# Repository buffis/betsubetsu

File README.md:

# BetsuBetsu

BetsuBetsu is an Open Source Audio+Video splitter for streaming/recording video from Arcade games (Jamma).

It plugs in between the game and cabinet, and can then be connected to any upscaler + PC for streaming/recording.

## Features
- MiniDIN 8 RGB video out (same pins as XRGB-Mini, HAS,...), for hooking it up to OSSC.
- Mono audio output through audio jack.
- Adjustable RGB video levels through onboard trimpots.
- Audio gain can be fine tuned through onboard trimpot.
- Power LED
- Optional Voltmeter can be attached

## More detailed features
- Line level audio conversion with galvanic isolation (TY-250P).
- Buffering and unbiasing of Video and Sync signals to safe levels (THS7374). Inputs and outputs are AC-coupled. Safe to drive 75ohm loads / OSSC.
- Audio completely isolated from video (no common ground) to avoid ground loop noise.

## Build instructions

- Order a pcb. Kicad plot files are in the plot/ subdir in the repo.
- Order all parts needed (see BOM)
- Solder it up (suggested order below)
  - Start with THS7374. It's the trickiest footprint to solder.
  - Then do all 0805-sized parts in any order.
  - Solder all five big capacitors. Note that the bottom one is 100uF
  - Solder all trimpots
  - Solder the transformer + output jacks
  - Finally add the Jamma connector (make sure to put it on Jamma In)
- (Optional) Add a voltmeter.

## Installation instructions

1. Insert the BetsuBetsu into the cab jamma harness and connect the game.
2. Connect "Audio Out" to the PC line-in with a stereo cable.
3. Connect "Video Out" to a OSSC or XRGB-Mini with a MINI-DIN8 to SCART cable
4. Connect OSSC/XRGB-Mini to a Capture card (I recomment USB3HDCAP)
5. Capture/Stream in OBS.
6. Calibrate strength of video signals with onboard trimpots
7. Audio output can be fine-adjusted with onboard "Audio" trimpot.

## Schematic (v1.0):

## Board:

## BOM:
https://docs.google.com/spreadsheets/d/1Nb6cgpz1vrsEBL83Tl52jcXvUmsp_AzcXZ7w7m8aYmA/edit?usp=sharing

## Sample capture:
BetsuBetsu + OSSC + Elgato 60 Pro. Scaled to fit inside 1080p in OBS.
Audio is wired from Betsu Betsu to PC Line in directly.
https://www.youtube.com/watch?v=HWDo_Xj9CUc

BetsuBetsu + XRGB-Mini + Elgato 60 Pro. Scaled to fit inside 1080p in OBS.
Audio is wired from Betsu Betsu to PC Line in directly.
https://www.youtube.com/watch?v=Qm8Wi2TviPc

## Misc links:
Arcade-projects thread:
https://www.arcade-projects.com/forums/index.php?thread/10551-betsu-betsu-open-source-arcade-audio-video-splitter-for-capture-streaming/

## Misc pics:
Action shot of prototype board in cab:

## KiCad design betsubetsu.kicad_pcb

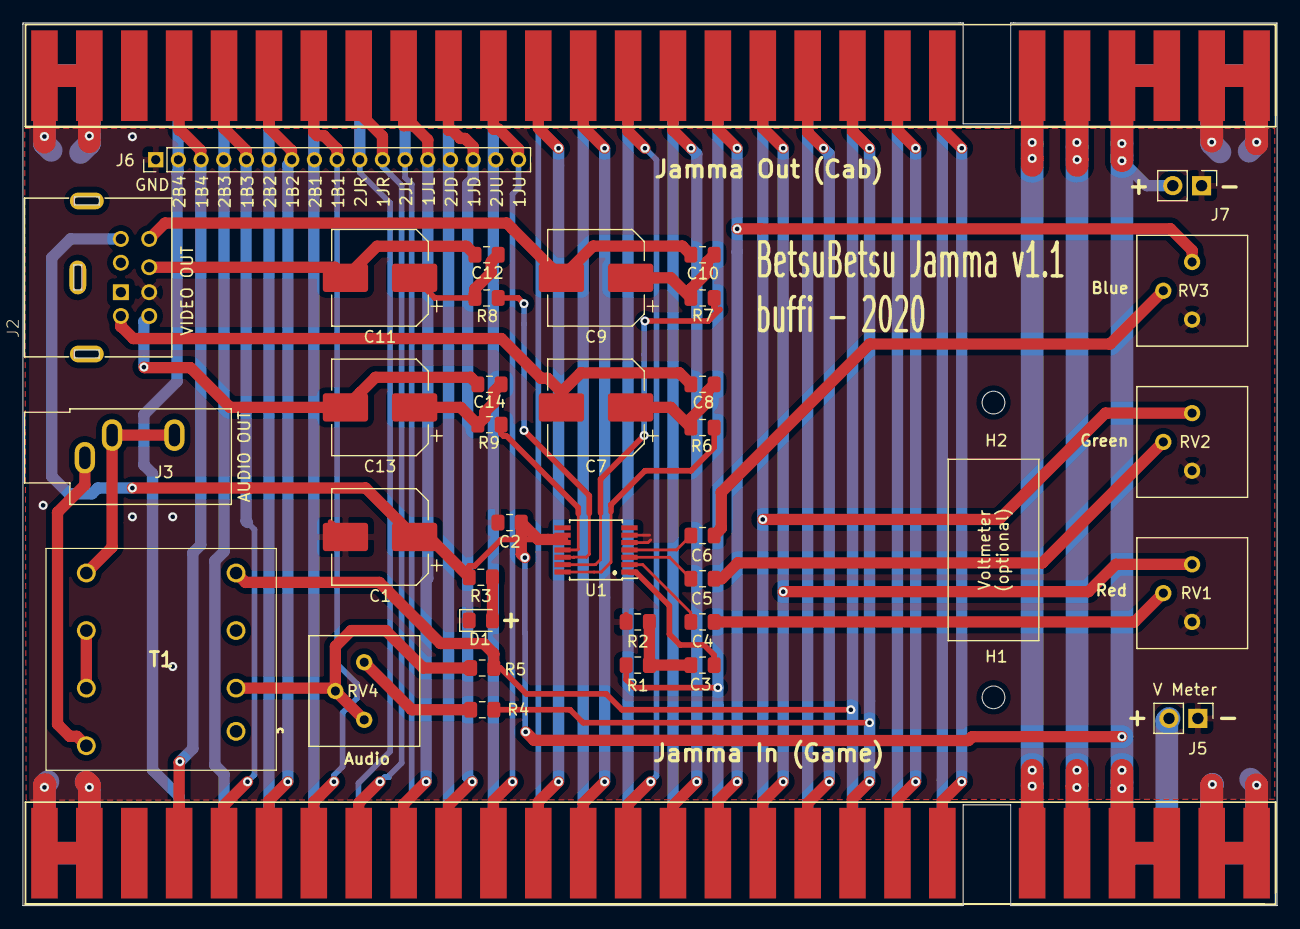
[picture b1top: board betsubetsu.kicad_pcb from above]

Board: 2 copper layers, 110.6 x 77.9 mm, 39 parts (0 on the bottom side), 66 nets.

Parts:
C1: 100u; CP_Elec_8x6.7
C2, C3, C4, C5, C6, C8, C10, C12, C14: 0.1u; C_0805_2012Metric_Pad1.15x1.40mm_HandSolder
C7, C9, C11, C13: 470u; CP_Elec_8x6.7
D1: LED; LED_0805_2012Metric_Pad1.15x1.40mm_HandSolder
H1, H2: V METER HOLE (2mm); MountingHole_2mm
J1: Jamma Out (Cab); JAMMA-56
J2: VIDEO OUT; MD-80SM
J3: AUDIO OUT; Jack_3.5mm_CUI_SJ1-3533NG_Horizontal
J4: Jamma In (Game); JAMMA-56
J5: V Meter; PinHeader_1x02_P2.54mm_Vertical
J6: Conn_01x17; PinHeader_1x17_P2.00mm_Vertical
J7: 5V; PinHeader_1x02_P2.54mm_Vertical
R1: 1k; R_0805_2012Metric_Pad1.15x1.40mm_HandSolder
R2: 150; R_0805_2012Metric_Pad1.15x1.40mm_HandSolder
R3, R4: 390; R_0805_2012Metric_Pad1.15x1.40mm_HandSolder
R5: 47; R_0805_2012Metric_Pad1.15x1.40mm_HandSolder
R6, R7, R8, R9: 75; R_0805_2012Metric_Pad1.15x1.40mm_HandSolder
RV1, RV2, RV3: 1K; Potentiometer_Bourns_3386P_Vertical
RV4: 500; Potentiometer_Bourns_3386P_Vertical
T1: TY-250P; TY250P
U1: THS7374; TSSOP-14_4.4x5mm_P0.65mm

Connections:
+5V: C1.1, C2.2, J1.3, J1.4, J1.C, J1.D, J2.5, J4.3, J4.4, J4.C, J4.D, J5.2, J7.2, R3.2, U1.9, U1.10
+12V: J1.6, J1.F, J4.6, J4.F
+AUDIO_IN: J1.10, J4.10, R4.1
-5V: J1.5, J1.E, J4.5, J4.E
-AUDIO_IN: J1.L, J4.L, R5.1, T1.4
BLUE_IN: J1.13, J4.13, RV3.1
BLUE_OUT: C13.2, C14.1, J2.6
COIN1: J1.16, J4.16
COIN2: J1.T, J4.T
CSYNC_OUT: C7.2, C8.1, J2.3
GND: C1.2, C2.1, D1.1, J1.1, J1.2, J1.27, J1.28, J1.A, J1.B, J1.e, J1.f, J2.4, J4.1, J4.2, J4.27, J4.28, J4.A, J4.B, J4.e, J4.f, J5.1, J6.1, J7.1, R2.1, RV1.3, RV2.3, RV3.3, U1.5, U1.6
GREEN_IN: J1.N, J4.N, RV2.1
GREEN_OUT: C11.2, C12.1, J2.7
LOCKOUT1: J1.9, J4.9
LOCKOUT2: J1.K, J4.K
METER1: J1.8, J4.8
METER2: J1.J, J4.J
unnamed: C3.1, U1.1
unnamed: C3.2, R1.1, R2.2
unnamed: C4.1, U1.2
unnamed: C4.2, RV1.2
unnamed: C5.1, U1.3
unnamed: C5.2, RV2.2
unnamed: C6.1, U1.4
unnamed: C6.2, RV3.2
unnamed: C7.1, C8.2, R6.1
unnamed: C9.1, C10.2, R7.1
unnamed: C11.1, C12.2, R8.1
unnamed: C13.1, C14.2, R9.1
unnamed: D1.2, R3.1
unnamed: J3.R, J3.T, T1.5
unnamed: J3.S, T1.8
unnamed: R4.2, RV4.1
unnamed: R5.2, RV4.2, RV4.3, T1.2
unnamed: R6.2, U1.14
unnamed: R7.2, U1.13
unnamed: R8.2, U1.12
unnamed: R9.2, U1.11
unnamed: T1.6, T1.7
P1_A: J1.22, J4.22, J6.9
P1_B: J1.23, J4.23, J6.7
P1_C: J1.24, J4.24, J6.5
P1_D: J1.25, J4.25, J6.3
P1_DOWN: J1.19, J4.19, J6.15
P1_LEFT: J1.20, J4.20, J6.13
P1_RIGHT: J1.21, J4.21, J6.11
P1_START: J1.17, J4.17
P1_UP: J1.18, J4.18, J6.17
P2_A: J1.Z, J4.Z, J6.8
P2_B: J1.a, J4.a, J6.6
P2_C: J1.b, J4.b, J6.4
P2_D: J1.c, J4.c, J6.2
P2_DOWN: J1.W, J4.W, J6.14
P2_LEFT: J1.X, J4.X, J6.12
P2_RIGHT: J1.Y, J4.Y, J6.10
P2_START: J1.U, J4.U
P2_UP: J1.V, J4.V, J6.16
RED_IN: J1.12, J4.12, RV1.1
RED_OUT: C9.2, C10.1, J2.8
SERVICE: J1.R, J4.R
SYNC_IN: J1.P, J4.P, R1.2
TEST: J1.15, J4.15
TILT: J1.S, J4.S
UNUSED11: J1.11, J4.11
UNUSED39: J1.M, J4.M
VIDEO_GND: J1.14, J4.14

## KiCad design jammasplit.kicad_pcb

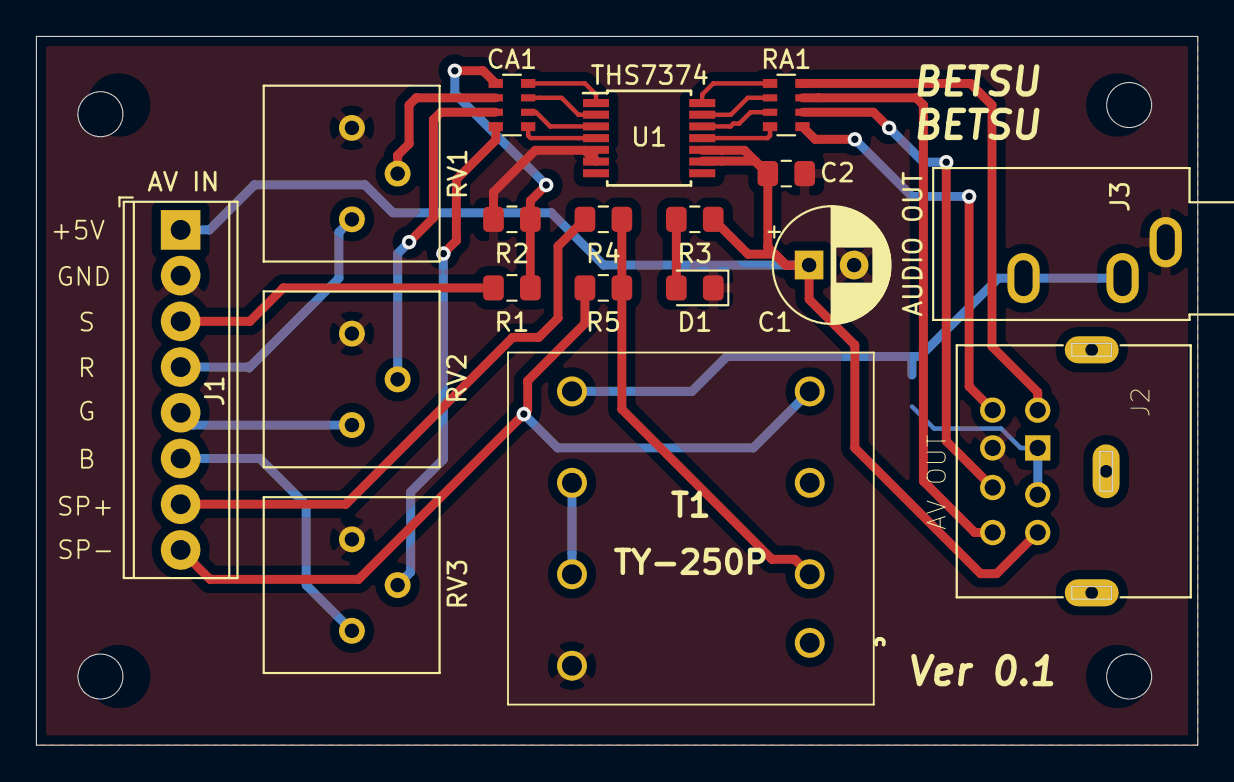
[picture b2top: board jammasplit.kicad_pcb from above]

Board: 2 copper layers, 64.5 x 39.4 mm, 23 parts (1 on the bottom side), 29 nets.

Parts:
C1: 100uF; CP_Radial_D6.3mm_P2.50mm
C2: 0.1uF; C_0805_2012Metric_Pad1.15x1.40mm_HandSolder
CA1: CapacitorArray4; R_Array_Convex_4x0603
D1: LED; LED_0805_2012Metric_Pad1.15x1.40mm_HandSolder
H1, H2, H3, H4: MountingHole; MountingHole_2.5mm
J1: AV IN; TerminalBlock_Phoenix_MPT-0,5-8-2.54_1x08_P2.54mm_Horizontal
J2: AV OUT; CUI_MD-80SM
J3: AUDIO OUT; Jack_3.5mm_CUI_SJ1-3533NG_Horizontal
JMP1: SCART_AUDIO; R_0603_1608Metric_Pad1.05x0.95mm_HandSolder
R1: 1k; R_0805_2012Metric_Pad1.15x1.40mm_HandSolder
R2: 150; R_0805_2012Metric_Pad1.15x1.40mm_HandSolder
R3, R4: 390; R_0805_2012Metric_Pad1.15x1.40mm_HandSolder
R5: 47; R_0805_2012Metric_Pad1.15x1.40mm_HandSolder
RA1: ResistorArray4; R_Array_Convex_4x0603
RV1, RV2, RV3: 1K; Potentiometer_Bourns_3386P_Vertical
T1: TY-250P; TY250P
U1: THS7374; TSSOP-14_4.4x5mm_P0.65mm

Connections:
+5V: C1.1, C2.2, J1.1, J2.5, R3.2, U1.9, U1.10
+AUDIO_IN: J1.7, R4.1
-AUDIO_IN: J1.8, R5.1, T1.4
AUDIO_MONO_OUT: J2.1, J2.2, JMP1.1
BLUE_IN: J1.6, RV3.1
BLUE_OUT: J2.6, RA1.5
CSYNC_OUT: J2.3, RA1.8
GND: C1.2, C2.1, D1.1, J1.2, J2.4, J3.S, R2.1, RV1.3, RV2.3, RV3.3, T1.8, U1.5, U1.6
GREEN_IN: J1.5, RV2.1
GREEN_OUT: J2.7, RA1.6
unnamed: CA1.1, R1.1, R2.2
unnamed: CA1.2, RV1.2
unnamed: CA1.3, RV2.2
unnamed: CA1.4, RV3.2
unnamed: CA1.5, U1.4
unnamed: CA1.6, U1.3
unnamed: CA1.7, U1.2
unnamed: CA1.8, U1.1
unnamed: D1.2, R3.1
unnamed: J3.R, J3.T, JMP1.2, T1.5
unnamed: R4.2, R5.2, T1.2
unnamed: RA1.1, U1.14
unnamed: RA1.2, U1.13
unnamed: RA1.3, U1.12
unnamed: RA1.4, U1.11
unnamed: T1.6, T1.7
RED_IN: J1.4, RV1.1
RED_OUT: J2.8, RA1.7
SYNC_IN: J1.3, R1.2

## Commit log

2019-09-09 v 0.1
    v 0.1
2019-09-20 small fixes
2019-09-21 Library cleanup
2019-09-21 v0.2
2019-09-22 Gerbers and cleanup
2019-09-22 Netlist
2019-09-22 fix typo
2020-05-14 jamma version
2020-05-14 Cleaned up jamma version
2020-05-26 EL1883 (if i need it later)
2020-06-10 New gerbers
